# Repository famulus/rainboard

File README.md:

# rainboard

An open-source isomorphic MIDI controller.

### Firmware Install:

The Rainboard firmware runs on an Arduino Mega which has two processors on board:
The main processor ( ATmega2560 ), and USB processor ( ATmega16U2 ). 

Requires an Arduino Mega with a 16U2 USB chip.

##### Installing the Rainboard firmware consists of two steps:

1. Flashing the USB controller, the ATmega16U2 with the `rainboard16U2.hex` file.
2. Uploading the main program `rainboard_firmware.ino` sketch to the Arduino Mega.

## Windows

#### Flash the USB Controller (ATmega16U2):

This can be accomplished with a DFU Programmer. Follow the instructions for your programmer.

Alternatively, if you don't have a DFU Programmer you can use Atmel FLIP software on a Windows Computer.

1. Go to http://www.atmel.com/tools/FLIP.aspx and download FLIP.
2. Install FLIP. Follow the installation wizard.
3. Disconnect Arduino from USB.
4. Jumper pins 5 and 6 on 16U2 ICSP header (as shown in fig.1). This will keep the 16U2 in RESET.

5. Connect Arduino to USB.
6. Remove the jumper from pins 5 and 6. At this moment, 16U2 goes into DFU mode. A new USB device should be recognized.
7. If driver is not installed automatically, install it from `c:\Program Files\AtmelFlip 3.4.7\usb\`
8. Go to Device manager (Win+Pause -> (Hardware) -> Device Manager) and check if you can see the driver installed correctly. It will be located under Atmel USB Devices -> ATmega16U2.
9. Disconnect Arduino from USB. Jumper pins 5 and 6.
10. Connect Arduino to USB.
11. Remove the jumper from pins 5 and 6.
12. Start FLIP Software: Go to Start -> All Programs -> Flip -> Flip.
13. Go to Settings -> Communication -> USB.
14. Press “Open”.
15. Go to File -> Load HEX file and select the `rainboard16U2.hex` file.
16.  Press “Run”. This will program the 16U2 with the `rainboard16U2.hex` file.
17. Now close FLIP, disconnect and reconnect the Arduino, it should be recognized as a MIDI  device named Rainboard.

#### Upload firmware to the Arduino Mega (ATmega2560):

The easiest way to upload the firmware through the Arduino IDE. 
Make sure you have the proper drivers installed and that you can program the Mega from the Arduino IDE. 
You will also need two Arduino libraries installed that the Rainboard firmware depends on:

`Adafruit-MCP23017-Arduino-Library` - https://github.com/adafruit/Adafruit-MCP23017-Arduino-Library

`MIDI_Library-5.0.2` -  https://github.com/FortySevenEffects/arduino_midi_library

Make sure your Arduino environment is working, you have the two libraries installed and you can successfully compile the `rainboard_firmware.ino` sketch.  
Also make sure you have already flashed the ATmega16U2 with the `rainboard16U2.hex` file per the previous step.

1. Power down the Arduino. (unplug from host Computer)
2. Connect a jumper across pins 4 and 6 on the ICSP Header of the 16U2 (as shown in fig.1).

3. Reconnect the Arduino to the host Computer. It should appear as a COM Port Device in the Arduino IDE.
4. Now you can compile and upload the rainboard_firmware.ino sketch to the Arduino in the standard way.
5. After programming, power down (unplug from host Computer), remove the jumper from pins 4 and 6 on the   ICSP Header of the 16U2 (as shown in fig.1). The Arduino should now be fully programmed and ready to mate to the Rainboard. 
6. **Be very careful that all the pins are aligned and inserted properly before fully mating!**
7. Once the Arduino is mated to the Rainboard, reconnect it to the host PC and it should appear as a MIDI Device with the name Rainboard.

## Mac OS X

#### Flash the USB Controller (ATmega16U2):

Requires homebrew: https://brew.sh/

`brew install avrdude`

`cd [rainboard directory]/rainboard-firmware`

`avrdude -p at90usb82 -F -P usb -c usbtiny -U flash:w:rainboard16u2.hex -U lfuse:w:0xFF:m -U hfuse:w:0xD9:m -U efuse:w:0xF4:m -U lock:w:0x0F:m`

#### Upload firmware to the Arduino Mega (ATmega2560):

Same instructions as Windows.

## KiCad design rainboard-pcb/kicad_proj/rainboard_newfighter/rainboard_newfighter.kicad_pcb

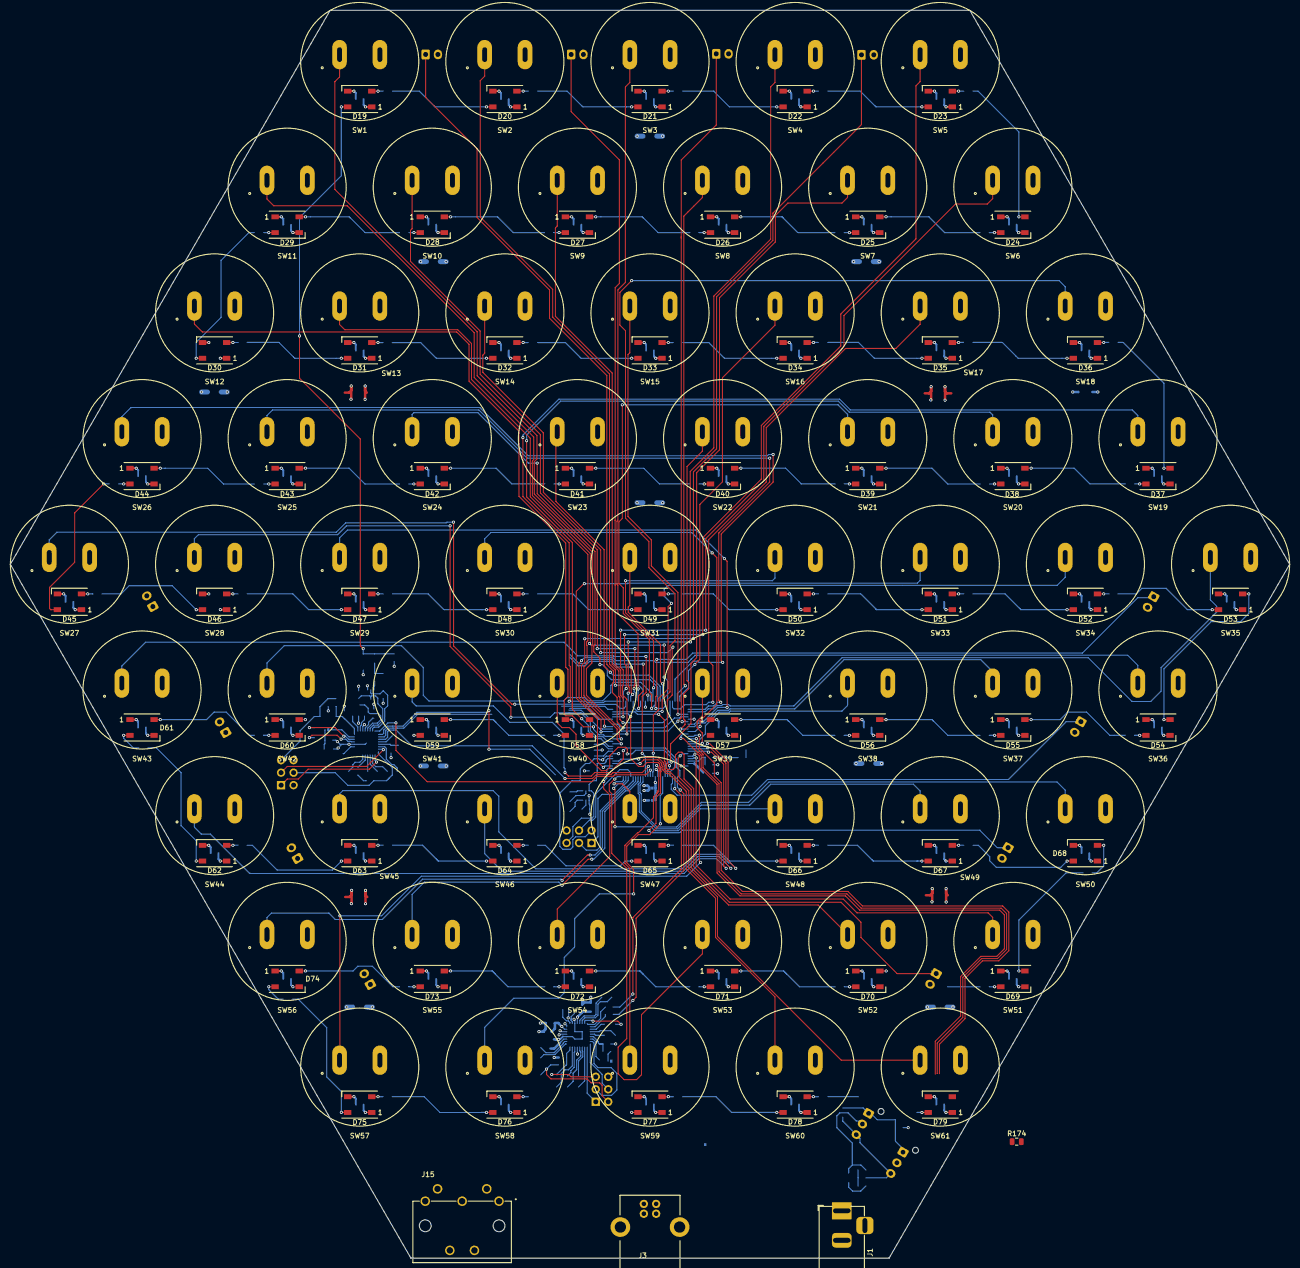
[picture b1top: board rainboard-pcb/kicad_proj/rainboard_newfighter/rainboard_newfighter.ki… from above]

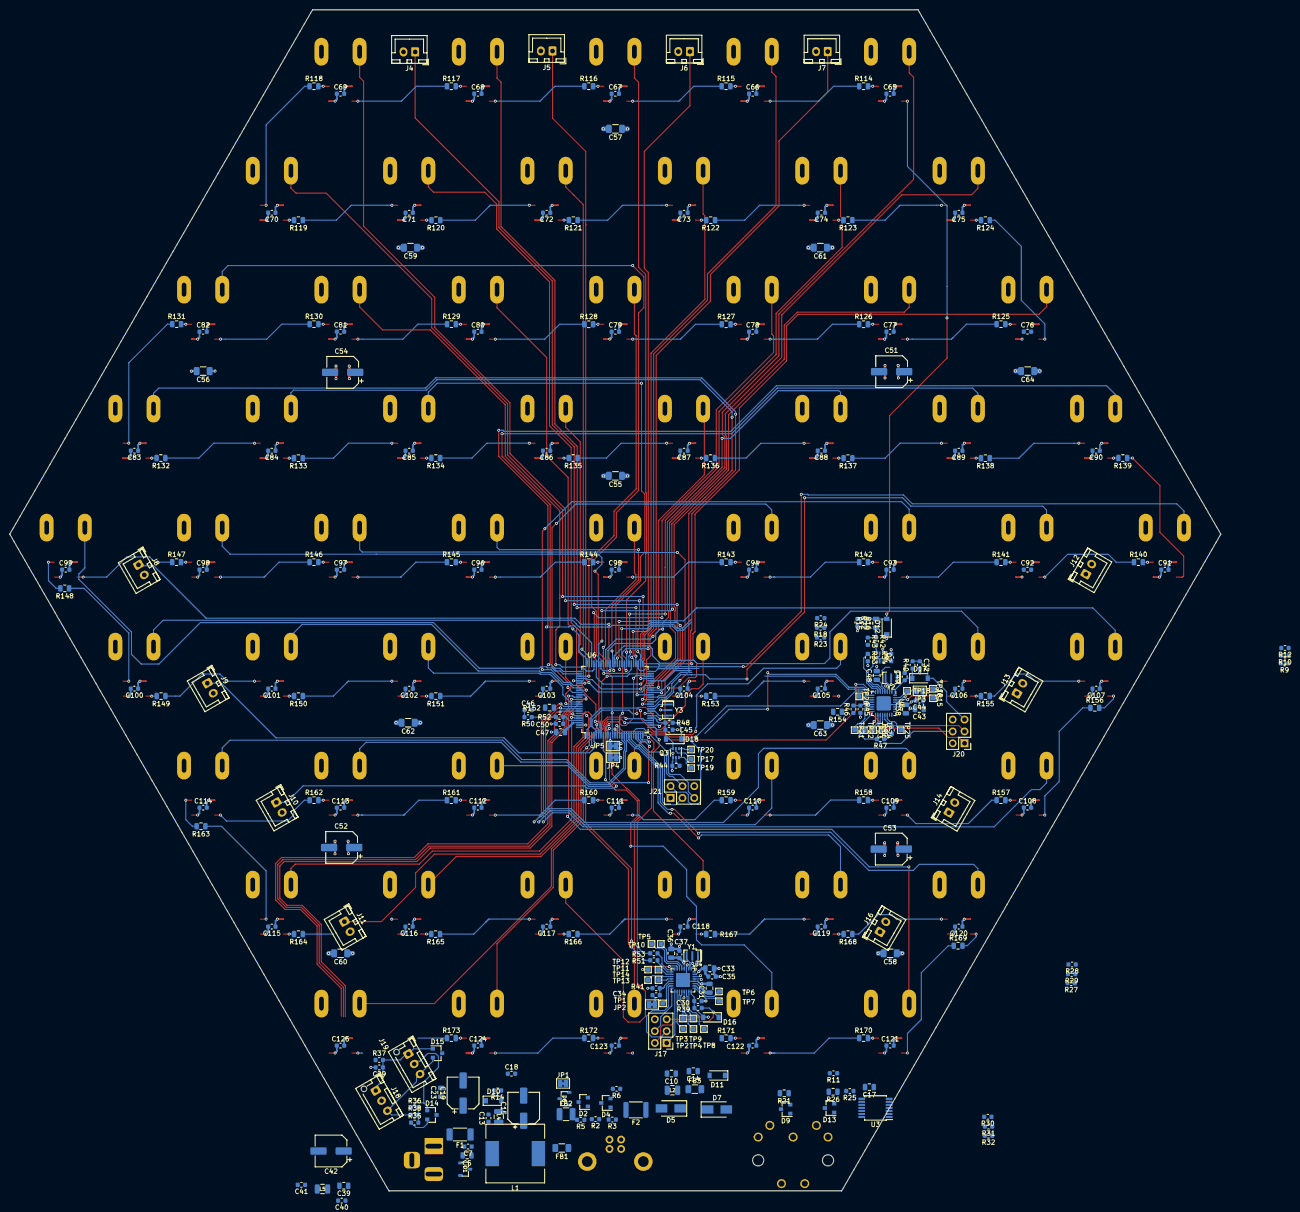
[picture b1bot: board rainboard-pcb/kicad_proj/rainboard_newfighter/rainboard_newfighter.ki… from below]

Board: 4 copper layers, 260.0 x 253.6 mm, 420 parts (294 on the bottom side), 301 nets.

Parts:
C5, C10, C14, C17, C23, C31, C33, C36, C38, C39, C43, C47, C48: 1uF 25V; C_0805_2012Metric
C7, C13, C18, C29, C30, C32, C34, C35, C37, C40, C41, C44, C45, C46, C49, C50, C65, C66, C67, C68, C69, C70, C71, C72, C73, C74, C75, C76, C77, C78, C79, C80, C81, C82, C83, C84, C85, C86, C87, C88, C89, C90, C91, C92, C93, C94, C95, C96, C97, C98, C99, C100, C101, C102, C103, C104, C105, C106, C107, C108, C109, C110, C111, C112, C113, C114, C115, C116, C117, C118, C119, C120, C121, C122, C123, C124, C125: 100nf; C_0603_1608Metric
C15, C19, C42, C51, C52, C53, C54: 470uF 10V; CP_Elec_6.3x7.7
C55, C56, C57, C58, C59, C60, C61, C62, C63, C64: 10uF 25V; C_1206_3216Metric
D1, D6: 6V; SOT23-3
D2, D4, D9, D13, D14, D15: 5Vw; SOT-23
D5, D7: 5Vw; D_SMA
D10, D11, D12, D16, D17, D18: 40V 1A; D_SOD-123
D19, D20, D21, D22, D23, D24, D25, D26, D27, D28, D29, D30, D31, D32, D33, D34, D35, D36, D37, D38, D39, D40, D41, D42, D43, D44, D45, D46, D47, D48, D49, D50, D51, D52, D53, D54, D55, D56, D57, D58, D59, D60, D61, D62, D63, D64, D65, D66, D67, D68, D69, D70, D71, D72, D73, D74, D75, D76, D77, D78, D79: WS2812B; LED_WS2812B_PLCC4_5.0x5.0mm_P3.2mm
F1: 12V 5A; Fuse_2010_5025Metric
F2: 15V .5A; Fuse_1812_4532Metric
FB1, FB3: 4A Ferrite; L_1206_3216Metric
FB2: 10A Ferrite; L_1210_3225Metric
J1: 54-00167; BarrelJack_Horizontal
J3: USB_B; UJ2-BH-1-TH
J4, J5, J6, J7, J8, J9, J10, J11, J12, J13, J14, J16: Conn_01x02_Female; JST_XH_B2B-XH-A_1x02_P2.50mm_Vertical
J15: SDS-50J; CUI_SDS-50J
J17, J20, J21: PH2-06-UA; PinHeader_2x03_P2.54mm_Vertical
J18, J19: Conn_01x03; JST_XH_B3B-XH-AM_1x03_P2.50mm_Vertical
JP1, JP2, JP3, JP4, JP5: Jumper; SolderJumper-2_P1.3mm_Bridged_Pad1.0x1.5mm
L1: 27uH; L_12x12mm_H8mm
L2, L4, L5: 10uH .5Ohm; INDC250X180X200L50N
Q2, Q3: DUAL 30V NMOS; SOT-363_SC-70-6
R2, R3, R5, R6, R11, R25, R42, R43, R47, R49, R51, R53: 11R; R_0603_1608Metric
R9, R18, R27, R30, R33, R34, R37, R38, R41, R44, R46: 4.7k; R_0603_1608Metric
R10, R12, R22, R23, R24, R28, R29, R31, R32, R39, R40, R48, R50, R52: 19.1k; R_0603_1608Metric
R14, R35, R36: 100k; R_0603_1608Metric
R15, R21, R26, R114, R115, R116, R117, R118, R119, R120, R121, R122, R123, R124, R125, R126, R127, R128, R129, R130, R131, R132, R133, R134, R135, R136, R137, R138, R139, R140, R141, R142, R143, R144, R145, R146, R147, R148, R149, R150, R151, R152, R153, R154, R155, R156, R157, R158, R159, R160, R161, R162, R163, R164, R165, R166, R167, R168, R169, R170, R171, R172, R173, R174: 210R; R_0805_2012Metric
R16: DNP-210R; R_0805_2012Metric
R45: DNP-4.7k; R_0603_1608Metric
SW1, SW2, SW3, SW4, SW5, SW6, SW7, SW8, SW9, SW10, SW11, SW12, SW13, SW14, SW15, SW16, SW17, SW18, SW19, SW20, SW21, SW22, SW23, SW24, SW25, SW26, SW27, SW28, SW29, SW30, SW31, SW32, SW33, SW34, SW35, SW36, SW37, SW38, SW39, SW40, SW41, SW42, SW43, SW44, SW45, SW46, SW47, SW48, SW49, SW50, SW51, SW52, SW53, SW54, SW55, SW56, SW57, SW58, SW59, SW60, SW61: SANWA-OBSF24; Sanwa-OBSF24-v2
TP1, TP2, TP3, TP4, TP5, TP6, TP7, TP8, TP9, TP10, TP11, TP12, TP13, TP14, TP15, TP16, TP17, TP18, TP19, TP20, TP21, TP22, TP23, TP24, TP25, TP26: TestPoint; TestPoint_Pad_1.0x1.0mm
U3: 74HC14; TSSOP-14_4.4x5mm_P0.65mm
U4: ATmega16U2-MU; QFN33P50_500X500X60L40X24T300N
U5: ATmega16U2-MU; QFN-32-1EP_5x5mm_P0.5mm_EP3.1x3.1mm
U6: ATmega2560-16AU; TQFP-100_14x14mm_P0.5mm
Y1, Y2, Y3: 16MHz; Resonator_SMD_muRata_CSTxExxV-3Pin_3.0x1.1mm

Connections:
5VA_MCU: C41.1, C42.1, L5.1, R37.1, U6.100
5V_MCU: C17.1, C19.1, C23.1, C36.1, C37.1, C39.1, C40.1, C48.1, C49.1, D10.1, D11.1, D16.1, D17.1, D18.1, J17.2, J20.2, J21.2, L5.2, R9.1, R18.1, R25.1, R27.1, R30.1, R39.1, R40.1, R46.1, R48.2, U3.14, U4.4, U4.32, U5.4, U5.32, U6.10, U6.31, U6.61, U6.80
5V_USB: C14.1, C33.1, C35.1, C43.1, C44.1, D7.1, D11.2, FB3.2, JP3.1, U4.31
5V_WALL: C13.1, C15.1, D6.3, FB2.1, JP1.1, L4.2, R14.1
/PCBMountButtons/FIRST_DIN: D12.2, D19.4, R15.2, R16.2, R22.1
/PCBMountButtons/sheet5FFC64B5/DIN: D35.4, R129.1
/PCBMountButtons/sheet5FFC64BB/DIN: D36.4, R130.1
/PCBMountButtons/sheet5FFC64CF/DIN: D37.4, R131.1
/PCBMountButtons/sheet5FFC64F0/DIN: D38.4, R132.1
/PCBMountButtons/sheet5FFC64F7/DIN: D39.4, R133.1
/PCBMountButtons/sheet5FFC646C/DIN: D32.4, R126.1
/PCBMountButtons/sheet5FFC651D/DIN: D41.4, R135.1
/PCBMountButtons/sheet5FFC6464/DIN: D31.4, R125.1
/PCBMountButtons/sheet5FFC6480/DIN: D33.4, R127.1
/PCBMountButtons/sheet5FFC6494/DIN: D34.4, R128.1
/PCBMountButtons/sheet5FFC6517/DIN: D40.4, R134.1
/PCBMountButtons/sheet5FFC6531/DIN: D42.4, R136.1
/PCBMountButtons/sheet5FFD98AC/DIN: D47.4, R141.1
/PCBMountButtons/sheet5FFD98B2/DIN: D48.4, R142.1
/PCBMountButtons/sheet5FFD98C6/DIN: D49.4, R143.1
/PCBMountButtons/sheet5FFD98E7/DIN: D50.4, R144.1
/PCBMountButtons/sheet5FFD98EE/DIN: D51.4, R145.1
/PCBMountButtons/sheet5FFD985B/DIN: D43.4, R137.1
/PCBMountButtons/sheet5FFD988B/DIN: D46.4, R140.1
/PCBMountButtons/sheet5FFD990E/DIN: D52.4, R146.1
/PCBMountButtons/sheet5FFD9863/DIN: D44.4, R138.1
/PCBMountButtons/sheet5FFD9877/DIN: D45.4, R139.1
/PCBMountButtons/sheet5FFD9914/DIN: D53.4, R147.1
/PCBMountButtons/sheet5FFD9928/DIN: D54.4, R148.1
/PCBMountButtons/sheet5FFFA9BC/DIN: D62.4, R156.1
/PCBMountButtons/sheet5FFFA9C3/DIN: D63.4, R157.1
/PCBMountButtons/sheet5FFFA9E3/DIN: D64.4, R158.1
/PCBMountButtons/sheet5FFFA9E9/DIN: D65.4, R159.1
/PCBMountButtons/sheet5FFFA9FD/DIN: D66.4, R160.1
/PCBMountButtons/sheet5FFFA94C/DIN: D57.4, R151.1
/PCBMountButtons/sheet5FFFA99B/DIN: D61.4, R155.1
/PCBMountButtons/sheet5FFFA930/DIN: D55.4, R149.1
/PCBMountButtons/sheet5FFFA938/DIN: D56.4, R150.1
/PCBMountButtons/sheet5FFFA960/DIN: D58.4, R152.1
/PCBMountButtons/sheet5FFFA981/DIN: D59.4, R153.1
/PCBMountButtons/sheet5FFFA987/DIN: D60.4, R154.1
/PCBMountButtons/sheet61ABE4BE/DIN: D21.4, R115.1
/PCBMountButtons/sheet61AC389A/DIN: D23.4, R117.1
/PCBMountButtons/sheet61AC3886/DIN: D22.4, R116.1
/PCBMountButtons/sheet61ACB861/DIN: D24.4, R118.1
/PCBMountButtons/sheet61ACB876/DIN: D25.4, R119.1
/PCBMountButtons/sheet61ACB899/DIN: D26.4, R120.1
/PCBMountButtons/sheet61AD1E3C/DIN: D27.4, R121.1
/PCBMountButtons/sheet61AD1E5E/DIN: D28.4, R122.1
/PCBMountButtons/sheet61AD1E64/DIN: D29.4, R123.1
/PCBMountButtons/sheet61AD1E79/DIN: D30.4, R124.1
/PCBMountButtons/sheet611F5592/DIN: D78.4, R172.1
/PCBMountButtons/sheet6001C1A7/DIN: D71.4, R165.1
/PCBMountButtons/sheet6001C1AD/DIN: D72.4, R166.1
/PCBMountButtons/sheet6001C1C1/DIN: D73.4, R167.1
/PCBMountButtons/sheet6001C1E2/DIN: D74.4, R168.1
/PCBMountButtons/sheet6001C1E9/DIN: D75.4, R169.1
/PCBMountButtons/sheet6001C15E/DIN: D68.4, R162.1
/PCBMountButtons/sheet6001C156/DIN: D67.4, R161.1
/PCBMountButtons/sheet6001C172/DIN: D69.4, R163.1
/PCBMountButtons/sheet6001C186/DIN: D70.4, R164.1
/PCBMountButtons/sheet6112CF44/DIN: D76.4, R170.1
/PCBMountButtons/sheet6019597E/DIN: D20.4, R114.1
/PCBMountButtons/sheet6120995A/DIN: D79.4, R173.1
/PCBMountButtons/sheet61155765/DIN: D77.4, R171.1
AREF: C29.1, C47.1, D15.1, J18.1, J19.1, R37.2, U6.98
BARREL_DETECT: C18.1, R14.2, R50.1, R52.1
BREF: D15.2, J18.3, J19.3, R38.1, U6.86
BTN1a: R10.1, U6.59
BTN1b: R12.1, U5.5
BTN2a: R23.1, U6.55
BTN2b: R24.1, U5.26
BTN3a: R28.1, U6.50
BTN3b: R29.1, U5.25
BTN4a: R31.1, U6.42
BTN4b: R32.1, U5.23
BTN5: SW1.1, U6.38
BTN6: SW2.1, U6.60
BTN7: SW3.1, U6.58
BTN8: SW4.1, U6.54
BTN9: SW5.1, U6.52
BTN10: SW6.1, U6.40
BTN11: SW7.1, U6.7
BTN12: SW8.1, U6.74
BTN13: SW9.1, U6.71
BTN14: SW10.1, U6.57
BTN15: SW11.1, U6.70
BTN16: SW12.1, U6.39
BTN17: SW13.1, U6.36
BTN18: SW14.1, U6.6
BTN19: SW15.1, U6.78
BTN20: SW16.1, U6.75
BTN21: SW17.1, U6.72
BTN22: SW18.1, U6.56
BTN23: SW19.1, U6.51
BTN24: SW20.1, U6.35
BTN25: SW21.1, U6.65
BTN26: SW22.1, U6.84
BTN27: SW23.1, U6.67
BTN28: SW24.1, U6.66
BTN29: SW25.1, U6.76
BTN30: SW26.1, U6.73
BTN31: SW27.1, U6.53
BTN32: SW28.1, U6.37
BTN33: SW29.1, U6.82
BTN34: SW30.1, U6.85
BTN35: SW31.1, U6.68
BTN36: SW32.1, U6.64
BTN37: SW33.1, U6.27
BTN38: SW34.1, U6.12
BTN39: SW35.1, U6.77
BTN40: SW36.1, U6.41
BTN41: SW37.1, U6.83
BTN42: SW38.1, U6.89
BTN43: SW39.1, U6.90
BTN44: SW40.1, U6.5
BTN45: SW41.1, U6.1
BTN46: SW42.1, U6.63
BTN47: SW43.1, U6.15
BTN48: SW44.1, U6.93
BTN49: SW45.1, U6.91
BTN50: SW46.1, U6.92
BTN51: SW47.1, U6.24
BTN52: SW48.1, U6.23
BTN53: SW49.1, U6.17
BTN54: SW50.1, U6.16
BTN55: SW51.1, U6.96
BTN56: SW52.1, U6.94
BTN57: SW53.1, U6.25
BTN58: SW54.1, U6.26
BTN59: SW55.1, U6.18
BTN60: SW56.1, U6.19
BTN61: SW57.1, U6.95
BTN62: SW58.1, U6.8
BTN63: SW59.1, U6.9
BTN64: SW60.1, U6.28
BTN65: SW61.1, U6.29
BTNX-1: J4.1, U6.43
BTNX-2: J5.1, U6.44
BTNX-3: J6.1, U6.47
BTNX-4: J10.1, U6.48
BTNX-5: J11.1, U6.49
BTNX-6: J7.1, U6.79
BTNX-7: J8.1, U6.69
BTNX-8: J9.1, U6.4
D+: D4.2, R5.1, U4.29
D-: D4.1, R6.1, U4.30
GND: C5.2, C7.2, C10.2, C13.2, C14.2, C15.2, C17.2, C18.2, C19.2, C23.2, C30.2, C31.2, C32.2, C33.2, C35.2, C36.2, C37.2, C38.2, C39.2, C40.2, C41.2, C42.2, C43.2, C44.2, C45.2, C46.2, C47.2, C48.2, C49.2, C50.2, C51.2, C52.2, C53.2, C54.2, C55.2, C56.2, C57.2, C58.2, C59.2, C60.2, C61.2, C62.2, C63.2, C64.2, C65.2, C66.2, C67.2, C68.2, C69.2, C70.2, C71.2, C72.2, C73.2, C74.2, C75.2, C76.2, C77.2, C78.2, C79.2, C80.2, C81.2, C82.2, C83.2, C84.2, C85.2, C86.2, C87.2, C88.2, C89.2, C90.2, C91.2, C92.2, C93.2, C94.2, C95.2, C96.2, C97.2, C98.2, C99.2, C100.2, C101.2, C102.2, C103.2, C104.2, C105.2, C106.2, C107.2, C108.2, C109.2, C110.2, C111.2, C112.2, C113.2, C114.2, C115.2, C116.2, C117.2, C118.2, C119.2, C120.2, C121.2, C122.2, C123.2, C124.2, C125.2, D1.1, D1.2, D2.3, D4.3, D5.2, D6.1, D6.2, D7.2, D9.3, D13.3, D14.3, D15.3, D19.3, D20.3, D21.3, D22.3, D23.3, D24.3, D25.3, D26.3, D27.3, D28.3, D29.3, D30.3, D31.3, D32.3, D33.3, D34.3, D35.3, D36.3, D37.3, D38.3, D39.3, D40.3, D41.3, D42.3, D43.3, D44.3, D45.3, D46.3, D47.3, D48.3, D49.3, D50.3, D51.3, D52.3, D53.3, D54.3, D55.3, D56.3, D57.3, D58.3, D59.3, D60.3, D61.3, D62.3, D63.3, D64.3, D65.3, D66.3, D67.3, D68.3, D69.3, D70.3, D71.3, D72.3, D73.3, D74.3, D75.3, D76.3, D77.3, D78.3, D79.3, FB1.1, J1.2, J1.3, J3.4, J4.2, J5.2, J6.2, J7.2, J8.2, J9.2, J10.2, J11.2, J12.2, J13.2, J14.2, J15.2, J15.S1, J15.S2, J16.2, J17.6, J20.6, J21.6, JP5.2, Q2.1, Q2.4, Q3.4, R22.2, R33.2, R34.2, R41.2, R44.2, R45.2, SW1.2, SW2.2, SW3.2, SW4.2, SW5.2, SW6.2, SW7.2, SW8.2, SW9.2, SW10.2, SW11.2, SW12.2, SW13.2, SW14.2, SW15.2, SW16.2, SW17.2, SW18.2, SW19.2, SW20.2, SW21.2, SW22.2, SW23.2, SW24.2, SW25.2, SW26.2, SW27.2, SW28.2, SW29.2, SW30.2, SW31.2, SW32.2, SW33.2, SW34.2, SW35.2, SW36.2, SW37.2, SW38.2, SW39.2, SW40.2, SW41.2, SW42.2, SW43.2, SW44.2, SW45.2, SW46.2, SW47.2, SW48.2, SW49.2, SW50.2, SW51.2, SW52.2, SW53.2, SW54.2, SW55.2, SW56.2, SW57.2, SW58.2, SW59.2, SW60.2, SW61.2, U3.5, U3.7, U3.9, U3.11, U3.13, U4.3, U4.28, U4.33, U5.3, U5.28, U5.33, Y1.2, Y2.2, Y3.2
GNDA: C29.2, JP4.1, R35.2, R36.2, R38.2
M8RXD: R51.1, U4.9
M8TXD: R53.1, U4.8
MCU1-MCU3_GPIO: U5.11, U6.14
MCU1-MCU3_TX: U5.8, U6.13
MCU1_MISO: J21.1, U6.22
MCU1_RST: C45.1, D18.2, J21.5, JP2.2, Q3.3, R48.1, U6.30
MCU1_SCK: J21.3, U6.20
MCU2_LED_CTRL: R16.1, R42.1, R43.1
MCU2_MISO2: J17.1, U4.17
MCU2_MOSI2: J17.4, Q2.3, R42.2, U4.16
MCU2_RST: C30.1, D16.2, J17.5, Q2.6, R39.2, U4.24
MCU2_SCK2: J17.3, U4.15
MCU3_LED_CTRL: R15.1, R47.1, R49.1
MCU3_MISO3: J20.1, U5.17
MCU3_MOSI3: J20.4, R47.2, U5.16
MCU3_RST: C32.1, D17.2, J20.5, R40.2, U5.24
MCU3_SCK3: J20.3, U5.15
MCU_MOSI: J21.4, U6.21
MIDI-OUT: U3.1, U6.46
unnamed: C5.1, C7.1, D1.3, F1.1, L1.2
unnamed: C10.1, D5.1, F2.1, L2.2
unnamed: C31.1, U4.27
unnamed: C34.1, R41.1, U4.13
unnamed: C34.2, JP2.1
unnamed: C38.1, U5.27
unnamed: C46.1, R50.2, U5.10
unnamed: C50.1, R52.2, U6.97
unnamed: D2.1, R3.1, R6.2
unnamed: D2.2, R2.1, R5.2
unnamed: D9.1, R11.1, R21.1
unnamed: D9.2, J15.5, R21.2
unnamed: D10.2, L4.1
unnamed: D13.1, J15.4, R26.2
unnamed: D13.2, R25.2, R26.1
unnamed: D19.2, R114.2
unnamed: D20.2, R115.2
unnamed: D21.2, R116.2
unnamed: D22.2, R117.2
unnamed: D23.2, R118.2
unnamed: D24.2, R119.2
unnamed: D25.2, R120.2
unnamed: D26.2, R121.2
unnamed: D27.2, R122.2
unnamed: D28.2, R123.2
unnamed: D29.2, R124.2
unnamed: D30.2, R125.2
unnamed: D31.2, R126.2
unnamed: D32.2, R127.2
unnamed: D33.2, R128.2
unnamed: D34.2, R129.2
unnamed: D35.2, R130.2
unnamed: D36.2, R131.2
unnamed: D37.2, R132.2
unnamed: D38.2, R133.2
unnamed: D39.2, R134.2
unnamed: D40.2, R135.2
unnamed: D41.2, R136.2
unnamed: D42.2, R137.2
unnamed: D43.2, R138.2
unnamed: D44.2, R139.2
unnamed: D45.2, R140.2
unnamed: D46.2, R141.2
unnamed: D47.2, R142.2
unnamed: D48.2, R143.2
unnamed: D49.2, R144.2
unnamed: D50.2, R145.2
unnamed: D51.2, R146.2
unnamed: D52.2, R147.2
unnamed: D53.2, R148.2
unnamed: D54.2, R149.2
unnamed: D55.2, R150.2
unnamed: D56.2, R151.2
unnamed: D57.2, R152.2
unnamed: D58.2, R153.2
unnamed: D59.2, R154.2
unnamed: D60.2, R155.2
unnamed: D61.2, R156.2
unnamed: D62.2, R157.2
unnamed: D63.2, R158.2
unnamed: D64.2, R159.2
unnamed: D65.2, R160.2
unnamed: D66.2, R161.2
unnamed: D67.2, R162.2
unnamed: D68.2, R163.2
unnamed: D69.2, R164.2
unnamed: D70.2, R165.2
unnamed: D71.2, R166.2
unnamed: D72.2, R167.2
unnamed: D73.2, R168.2
unnamed: D74.2, R169.2
unnamed: D75.2, R170.2
unnamed: D76.2, R171.2
unnamed: D77.2, R172.2
unnamed: D78.2, R173.2
unnamed: D79.2, R174.2
unnamed: F1.2, J1.1
unnamed: F2.2, J3.1
unnamed: FB1.2, J3.5
unnamed: FB2.2, L1.1
unnamed: FB3.1, L2.1
unnamed: J3.2, R3.2
unnamed: J3.3, R2.2
unnamed: J12.1, R9.2, R10.2, R12.2
unnamed: J13.1, R18.2, R23.2, R24.2
unnamed: J14.1, R27.2, R28.2, R29.2
unnamed: J16.1, R30.2, R31.2, R32.2
unnamed: JP3.2, TP18.1, U5.31
unnamed: JP4.2, JP5.1, U6.11, U6.32, U6.62, U6.81, U6.99
unnamed: Q3.1, TP20.1
unnamed: Q3.2, TP17.1
unnamed: Q3.6, TP19.1
unnamed: R11.2, U3.4
unnamed: R43.2, U4.21
unnamed: R45.1, R46.2, U5.13
unnamed: R49.2, U5.21
unnamed: R51.2, U6.2
unnamed: R53.2, U6.3
unnamed: TP1.1, U4.14
unnamed: TP2.1, U4.18
unnamed: TP3.1, U4.19
unnamed: TP4.1, U4.20
unnamed: TP5.1, U4.5
unnamed: TP6.1, U4.26
unnamed: TP7.1, U4.25
unnamed: TP8.1, U4.23
unnamed: TP9.1, U4.22
unnamed: TP10.1, U4.6
unnamed: TP11.1, U4.7
unnamed: TP12.1, U4.10
unnamed: TP13.1, U4.11
unnamed: TP14.1, U4.12
unnamed: TP15.1, U5.29
unnamed: TP16.1, U5.30
unnamed: TP21.1, U5.14
unnamed: TP22.1, U5.18
unnamed: TP23.1, U5.19
unnamed: TP24.1, U5.20
unnamed: TP25.1, U5.22
unnamed: TP26.1, U5.12
unnamed: U3.2, U3.3
unnamed: U4.1, Y1.1
unnamed: U4.2, Y1.3
unnamed: U5.1, Y2.1
unnamed: U5.2, Y2.3
unnamed: U6.33, Y3.3
unnamed: U6.34, Y3.1
PROG_CTRL_1: Q2.2, R33.1, U5.7
PROG_CTRL_2: Q2.5, R34.1, U5.6
RST_2560: Q3.5, R44.1, U5.9
VLED: C51.1, C52.1, C53.1, C54.1, C55.1, C56.1, C57.1, C58.1, C59.1, C60.1, C61.1, C62.1, C63.1, C64.1, C65.1, C66.1, C67.1, C68.1, C69.1, C70.1, C71.1, C72.1, C73.1, C74.1, C75.1, C76.1, C77.1, C78.1, C79.1, C80.1, C81.1, C82.1, C83.1, C84.1, C85.1, C86.1, C87.1, C88.1, C89.1, C90.1, C91.1, C92.1, C93.1, C94.1, C95.1, C96.1, C97.1, C98.1, C99.1, C100.1, C101.1, C102.1, C103.1, C104.1, C105.1, C106.1, C107.1, C108.1, C109.1, C110.1, C111.1, C112.1, C113.1, C114.1, C115.1, C116.1, C117.1, C118.1, C119.1, C120.1, C121.1, C122.1, C123.1, C124.1, C125.1, D12.1, D19.1, D20.1, D21.1, D22.1, D23.1, D24.1, D25.1, D26.1, D27.1, D28.1, D29.1, D30.1, D31.1, D32.1, D33.1, D34.1, D35.1, D36.1, D37.1, D38.1, D39.1, D40.1, D41.1, D42.1, D43.1, D44.1, D45.1, D46.1, D47.1, D48.1, D49.1, D50.1, D51.1, D52.1, D53.1, D54.1, D55.1, D56.1, D57.1, D58.1, D59.1, D60.1, D61.1, D62.1, D63.1, D64.1, D65.1, D66.1, D67.1, D68.1, D69.1, D70.1, D71.1, D72.1, D73.1, D74.1, D75.1, D76.1, D77.1, D78.1, D79.1, JP1.2
softpot-1: D14.2, J18.2, R35.1, U6.88
softpot-2: D14.1, J19.2, R36.1, U6.87

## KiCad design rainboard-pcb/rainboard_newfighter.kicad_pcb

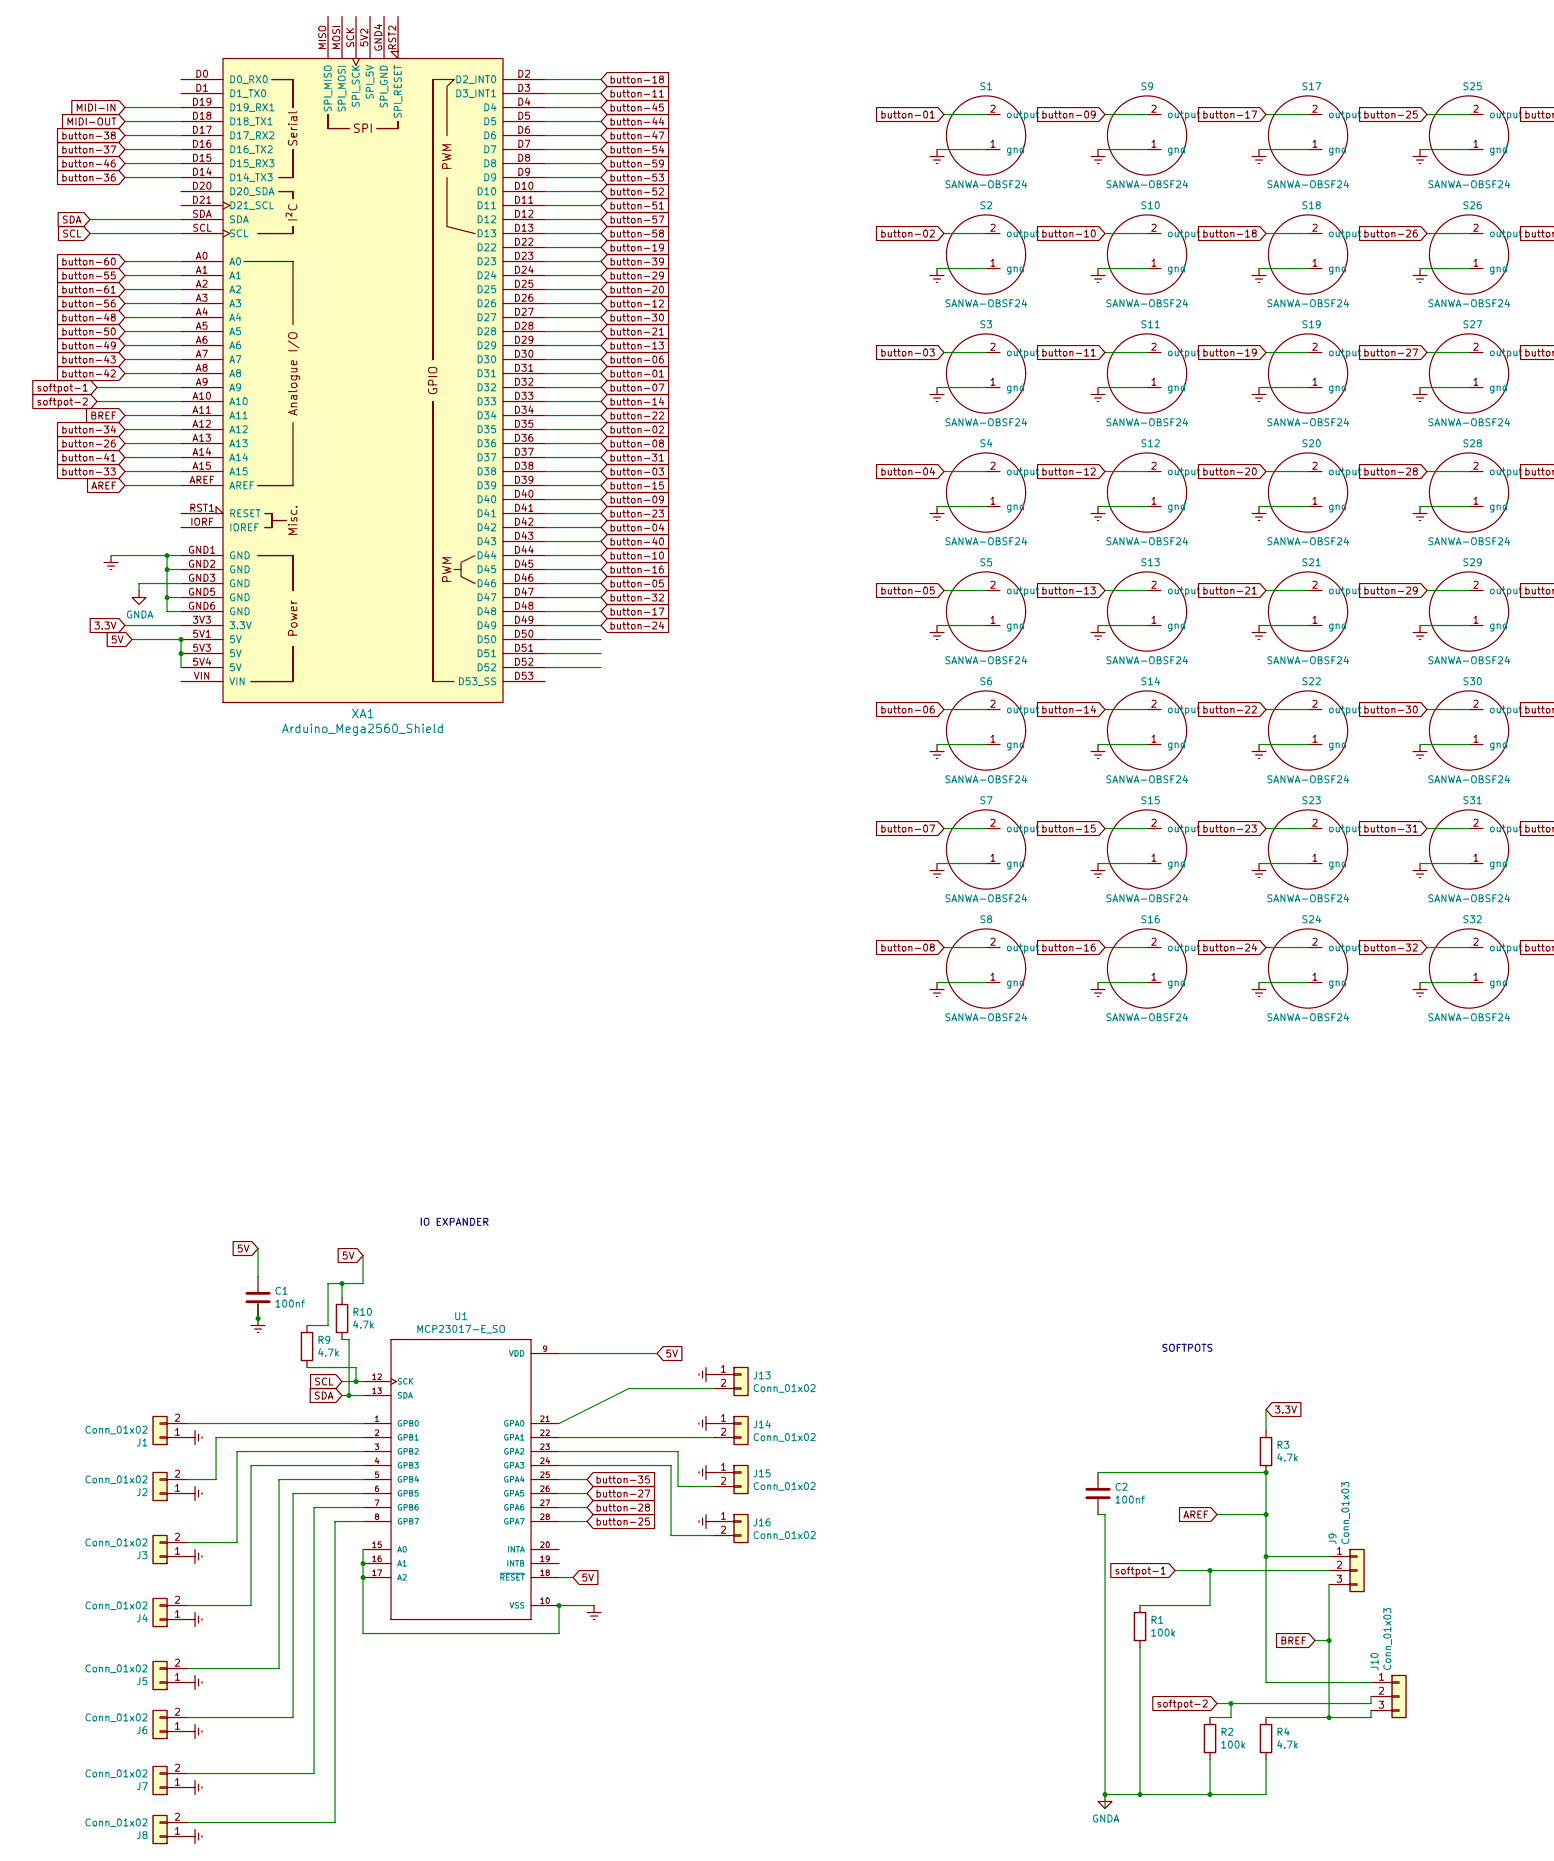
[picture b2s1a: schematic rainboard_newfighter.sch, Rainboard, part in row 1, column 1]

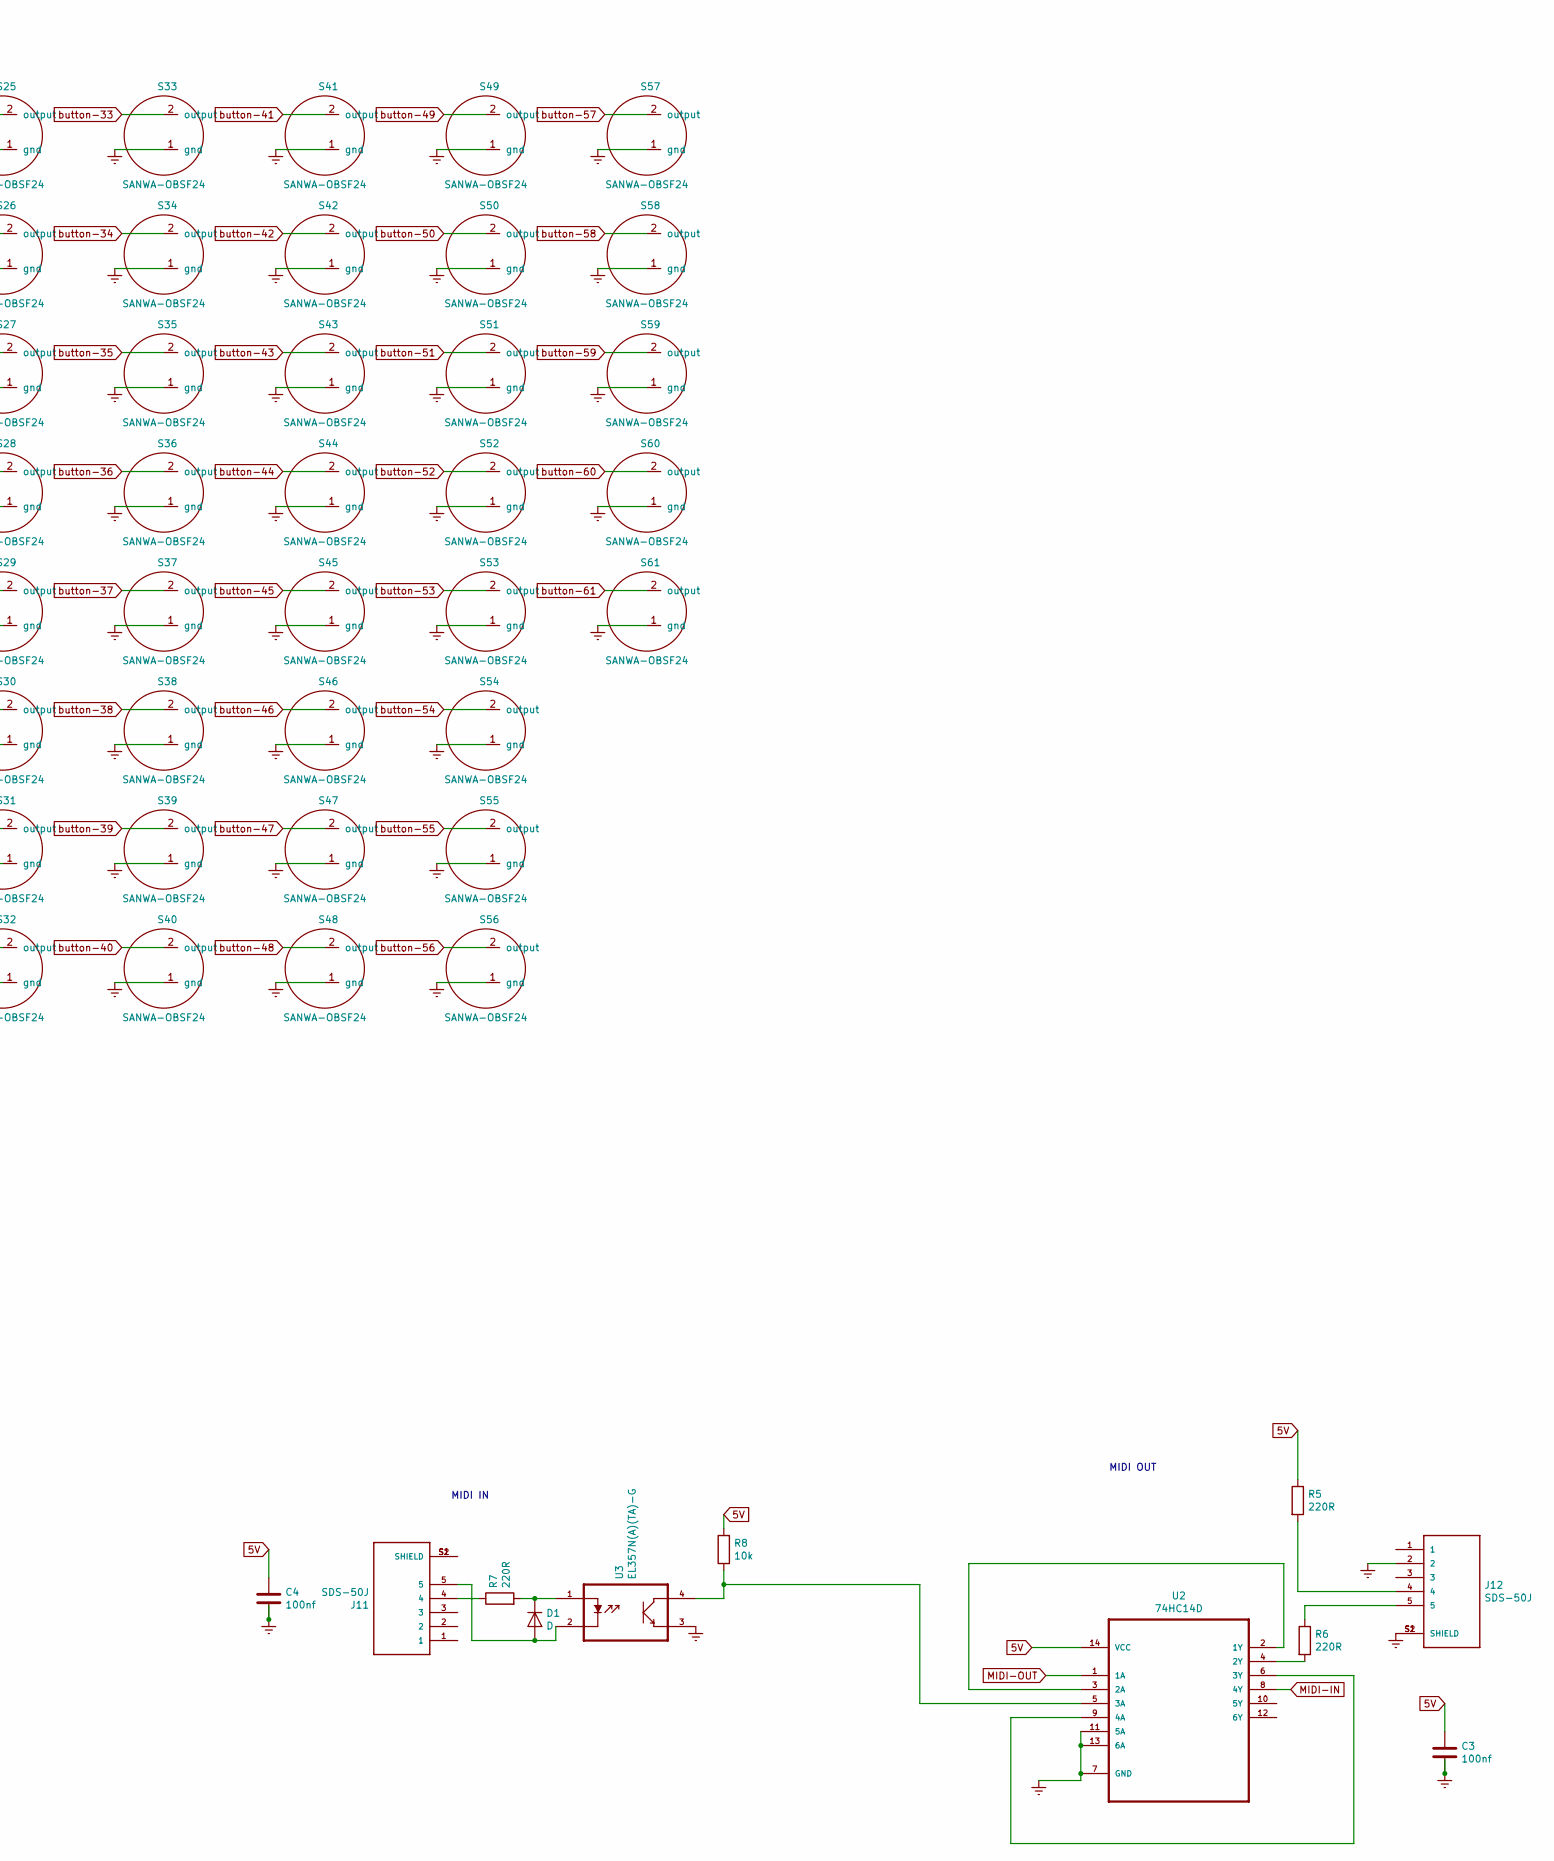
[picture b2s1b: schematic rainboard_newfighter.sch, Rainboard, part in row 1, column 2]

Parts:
C1, C2, C3, C4: 100nf; C_0603_1608Metric; LCSC C14663
D1: D; D_SMA; LCSC C95872
J1, J2, J3, J4, J5, J6, J7, J8, J13, J14, J15, J16: Conn_01x02; JST_XH_B2B-XH-AM_1x02_P2.50mm_Vertical
J9, J10: Conn_01x03; JST_XH_B3B-XH-AM_1x03_P2.50mm_Vertical
J11, J12: SDS-50J; CUI_SDS-50J
R1, R2: 100k; R_0603_1608Metric; LCSC C25803
R3, R4, R9, R10: 4.7k; R_0603_1608Metric; LCSC C23162
R5, R6, R7: 220R; R_0603_1608Metric; LCSC C22962
R8: 10k; R_0603_1608Metric; LCSC C25804
S1, S2, S3, S4, S5, S6, S7, S8, S9, S10, S11, S12, S13, S14, S15, S16, S17, S18, S19, S20, S21, S22, S23, S24, S25, S26, S27, S28, S29, S30, S31, S32, S33, S34, S35, S36, S37, S38, S39, S40, S41, S42, S43, S44, S45, S46, S47, S48, S49, S50, S51, S52, S53, S54, S55, S56, S57, S58, S59, S60, S61: SANWA-OBSF24; Sanwa-OBSF24-v2
U1: MCP23017-E_SO; SOIC127P1030X265-28N; LCSC C47023
U2: 74HC14D; SOIC127P600X175-14N; LCSC C5605
U3: EL357N(A)(TA)-G; SOP254P700X200-4N; LCSC C142286
XA1: Arduino_Mega2560_Shield

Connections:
3.3V: R3.1, XA1.3V3 (3.3V)
5V: C1.1, C3.1, C4.1, R5.1, R8.2, R9.1, R10.1, U1.9 (VDD), U1.18 (~RESET~), U2.14 (VCC), XA1.5V1 (5V), XA1.5V3 (5V), XA1.5V4 (5V)
AREF: C2.1, J9.1, J10.1, R3.2, XA1.AREF
BREF: J9.3, J10.3, R4.1, XA1.A11
Earth: C1.2, C3.2, C4.2, J1.1, J2.1, J3.1, J4.1, J5.1, J6.1, J7.1, J8.1, J12.2, J12.S1 (SHIELD), J12.S2 (SHIELD), J13.1, J14.1, J15.1, J16.1, S1.1 (gnd), S2.1 (gnd), S3.1 (gnd), S4.1 (gnd), S5.1 (gnd), S6.1 (gnd), S7.1 (gnd), S8.1 (gnd), S9.1 (gnd), S10.1 (gnd), S11.1 (gnd), S12.1 (gnd), S13.1 (gnd), S14.1 (gnd), S15.1 (gnd), S16.1 (gnd), S17.1 (gnd), S18.1 (gnd), S19.1 (gnd), S20.1 (gnd), S21.1 (gnd), S22.1 (gnd), S23.1 (gnd), S24.1 (gnd), S25.1 (gnd), S26.1 (gnd), S27.1 (gnd), S28.1 (gnd), S29.1 (gnd), S30.1 (gnd), S31.1 (gnd), S32.1 (gnd), S33.1 (gnd), S34.1 (gnd), S35.1 (gnd), S36.1 (gnd), S37.1 (gnd), S38.1 (gnd), S39.1 (gnd), S40.1 (gnd), S41.1 (gnd), S42.1 (gnd), S43.1 (gnd), S44.1 (gnd), S45.1 (gnd), S46.1 (gnd), S47.1 (gnd), S48.1 (gnd), S49.1 (gnd), S50.1 (gnd), S51.1 (gnd), S52.1 (gnd), S53.1 (gnd), S54.1 (gnd), S55.1 (gnd), S56.1 (gnd), S57.1 (gnd), S58.1 (gnd), S59.1 (gnd), S60.1 (gnd), S61.1 (gnd), U1.10 (VSS), U1.15 (A0), U1.16 (A1), U1.17 (A2), U2.7 (GND), U2.11 (5A), U2.13 (6A), U3.3, XA1.GND1 (GND), XA1.GND2 (GND), XA1.GND5 (GND), XA1.GND6 (GND)
GNDA: C2.2, R1.2, R2.2, R4.2, XA1.GND3 (GND)
MIDI-IN: U2.8 (4Y), XA1.D19 (D19_RX1)
MIDI-OUT: U2.1 (1A), XA1.D18 (D18_TX1)
unnamed: D1.1 (K), R7.2, U3.1
unnamed: D1.2 (A), J11.5, U3.2
unnamed: J1.2, U1.1 (GPB0)
unnamed: J2.2, U1.2 (GPB1)
unnamed: J3.2, U1.3 (GPB2)
unnamed: J4.2, U1.4 (GPB3)
unnamed: J5.2, U1.5 (GPB4)
unnamed: J6.2, U1.6 (GPB5)
unnamed: J7.2, U1.7 (GPB6)
unnamed: J8.2, U1.8 (GPB7)
unnamed: J11.4, R7.1
unnamed: J11.S1 (SHIELD), J11.S2 (SHIELD)
unnamed: J12.4, R5.2
unnamed: J12.5, R6.1
unnamed: J13.2, U1.21 (GPA0)
unnamed: J14.2, U1.22 (GPA1)
unnamed: J15.2, U1.23 (GPA2)
unnamed: J16.2, U1.24 (GPA3)
unnamed: R6.2, U2.4 (2Y)
unnamed: R8.1, U2.5 (3A), U3.4
unnamed: U2.2 (1Y), U2.3 (2A)
unnamed: U2.6 (3Y), U2.9 (4A)
SCL: R9.2, U1.12 (SCK), XA1.SCL
SDA: R10.2, U1.13 (SDA), XA1.SDA
button-01: S1.2 (output), XA1.D31
button-02: S2.2 (output), XA1.D35
button-03: S3.2 (output), XA1.D38
button-04: S4.2 (output), XA1.D42
button-05: S5.2 (output), XA1.D46
button-06: S6.2 (output), XA1.D30
button-07: S7.2 (output), XA1.D32
button-08: S8.2 (output), XA1.D36
button-09: S9.2 (output), XA1.D40
button-10: S10.2 (output), XA1.D44
button-11: S11.2 (output), XA1.D3 (D3_INT1)
button-12: S12.2 (output), XA1.D26
button-13: S13.2 (output), XA1.D29
button-14: S14.2 (output), XA1.D33
button-15: S15.2 (output), XA1.D39
button-16: S16.2 (output), XA1.D45
button-17: S17.2 (output), XA1.D48
button-18: S18.2 (output), XA1.D2 (D2_INT0)
button-19: S19.2 (output), XA1.D22
button-20: S20.2 (output), XA1.D25
button-21: S21.2 (output), XA1.D28
button-22: S22.2 (output), XA1.D34
button-23: S23.2 (output), XA1.D41
button-24: S24.2 (output), XA1.D49
button-25: S25.2 (output), U1.28 (GPA7)
button-26: S26.2 (output), XA1.A13
button-27: S27.2 (output), U1.26 (GPA5)
button-28: S28.2 (output), U1.27 (GPA6)
button-29: S29.2 (output), XA1.D24
button-30: S30.2 (output), XA1.D27
button-31: S31.2 (output), XA1.D37
button-32: S32.2 (output), XA1.D47
button-33: S33.2 (output), XA1.A15
button-34: S34.2 (output), XA1.A12
button-35: S35.2 (output), U1.25 (GPA4)
button-36: S36.2 (output), XA1.D14 (D14_TX3)
button-37: S37.2 (output), XA1.D16 (D16_TX2)
button-38: S38.2 (output), XA1.D17 (D17_RX2)
button-39: S39.2 (output), XA1.D23
button-40: S40.2 (output), XA1.D43
button-41: S41.2 (output), XA1.A14
button-42: S42.2 (output), XA1.A8
button-43: S43.2 (output), XA1.A7
button-44: S44.2 (output), XA1.D5
button-45: S45.2 (output), XA1.D4
button-46: S46.2 (output), XA1.D15 (D15_RX3)
button-47: S47.2 (output), XA1.D6
button-48: S48.2 (output), XA1.A4
button-49: S49.2 (output), XA1.A6
button-50: S50.2 (output), XA1.A5
button-51: S51.2 (output), XA1.D11
button-52: S52.2 (output), XA1.D10
button-53: S53.2 (output), XA1.D9
button-54: S54.2 (output), XA1.D7
button-55: S55.2 (output), XA1.A1
button-56: S56.2 (output), XA1.A3
button-57: S57.2 (output), XA1.D12
button-58: S58.2 (output), XA1.D13
button-59: S59.2 (output), XA1.D8
button-60: S60.2 (output), XA1.A0
button-61: S61.2 (output), XA1.A2
softpot-1: J9.2, R1.1, XA1.A9
softpot-2: J10.2, R2.1, XA1.A10

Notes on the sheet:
MIDI IN
MIDI OUT
SOFTPOTS
IO EXPANDER
